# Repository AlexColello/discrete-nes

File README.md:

# Discrete NES - Every Gate Visible

A discrete logic implementation of the Nintendo Entertainment System where **EVERY single gate output and EVERY memory bit is visible via LED**. Watch a complete NES flip every bit in real-time.

## Project Vision

This is an educational and artistic hardware project showcasing the complete internal state of a working NES using **TI Little Logic (SN74LVC1G) in DSBGA packages** — tiny ICs with the **bare silicon die visible** on top. Thousands of exposed silicon dies interspersed with glowing 0402 SMD LEDs.

**This is one of the largest discrete logic projects ever attempted:**
- Estimated **10,000+ LEDs** across all boards
- **Thousands of single-gate ICs** (TI Little Logic, DSBGA — bare silicon visible)
- Multiple PCBs with SMD assembly
- Complete **cycle-accurate NES** implementation in visible discrete logic

## The Aesthetic

Each logic gate is a single DSBGA package (1.75 x 1.25mm) with the bare silicon wafer pattern visible on top. Between them, tiny 0402 SMD LEDs (1.0 x 0.5mm) glow to show every gate output state. The LEDs are deliberately smaller than the ICs so the silicon dies are the visual focus.

## Board Structure

- **RAM Board** - 8-byte prototype (starting point, validates DSBGA assembly)
  - ~180 DSBGA ICs, ~115 LEDs, ~115 resistors
  - ~60x80mm PCB

- **CPU Board** (2A03 - 6502-based with APU)
  - ~5,000 LEDs, ~5,000 ICs

- **PPU Board** (2C02 - Picture Processing Unit)
  - ~3,000 LEDs, ~3,000 ICs

- **Glue Logic/Interconnect Boards**

## Technology Stack

- **Logic ICs:** TI Little Logic SN74LVC1G series (DSBGA — bare silicon die visible)
- **LEDs:** 0402 SMD (smaller than ICs for aesthetic balance)
- **LED Drive:** Direct from LVC outputs (up to 24mA capable, target 2mA)
- **Schematic Generation:** Python + kiutils
- **PCB Layout:** kiutils + manual routing
- **Logic Reference:** MiSTer NES core (Verilog/SystemVerilog)
- **Design Tool:** KiCad 8.x
- **Assembly:** Solder paste stencil + hot air reflow

## Repository Structure

```
discrete-nes/
├── shared/               # Shared libraries and utilities
│   ├── kicad-lib/       # KiCad symbols, footprints, 3D models
│   └── python/          # Python generation utilities
├── boards/              # Individual board projects
│   ├── ram-prototype/   # First prototype board (8 bytes)
│   ├── cpu-2a03/        # CPU board
│   ├── ppu-2c02/        # PPU board
│   └── interconnect/    # Board interconnection
├── reference/           # FPGA reference documentation
└── tools/               # Development tools
```

## Getting Started

### Prerequisites

- Python 3.8+
- KiCad 8.x
- Git

### Setup

1. **Clone this repository:**
   ```bash
   git clone https://github.com/yourusername/discrete-nes.git
   cd discrete-nes
   ```

2. **Set up Python environment:**
   ```bash
   python -m venv venv
   source venv/bin/activate  # On Windows: venv\Scripts\activate
   pip install -r requirements.txt
   ```

3. **Review the reference documentation:**
   See `reference/README.md` for information about accessing the MiSTer NES core used as logic reference.

## Development Workflow

1. **Design circuit manually** in KiCad (first cell/module)
2. **Document the pattern** for script generation
3. **Write Python scripts** to generate repetitive structures
4. **Generate schematics** using kiutils
5. **Place components** on PCB (scripted DSBGA grid layout)
6. **Route manually** or use assisted tools
7. **Validate** with DRC/ERC
8. **Fabricate and reflow assemble**

## Current Status

**Phase 1: Project Setup** - COMPLETE

- [x] Repository structure created
- [x] Python utilities framework
- [x] Reference documentation
- [x] KiCad shared libraries (symbols/footprints)
- [x] Migration to TI Little Logic DSBGA
- [ ] RAM prototype circuit design (next)

## Power Requirements

With an LED on every gate output, power consumption is LED-dominated:

- RAM prototype (8 bytes): ~0.25A at 3.3V (~0.8W)
- Full system: ~12A+ at 3.3V (~40W)

## Educational Value

This project provides unparalleled visibility into:
- How a CPU executes instructions (watch the program counter increment!)
- Memory addressing and data flow
- Video frame generation in real-time
- Every internal state transition

Perfect for computer science education, maker spaces, and museum exhibits.

## Resources

- **MiSTer NES Core:** https://github.com/MiSTer-devel/NES_MiSTer (logic reference)
- **OpenTendo:** https://github.com/Redherring32/OpenTendo (NES reproduction PCBs)
- **NES Dev Wiki:** https://www.nesdev.org/wiki/
- **Visual 6502:** http://www.visual6502.org/

## Contributing

This is an ambitious project that will evolve over time. Contributions welcome:
- Circuit design improvements
- Python generation utilities
- Documentation
- Testing and validation

## License

TBD - To be determined

## Acknowledgments

- **MiSTer Project** - For the excellent NES core used as logic reference
- **Texas Instruments** - For the Little Logic product line
- **KiCad Project** - For the outstanding open-source EDA tools
- **Ben Eater** - For inspiring discrete logic projects
- **NES Dev Community** - For extensive documentation

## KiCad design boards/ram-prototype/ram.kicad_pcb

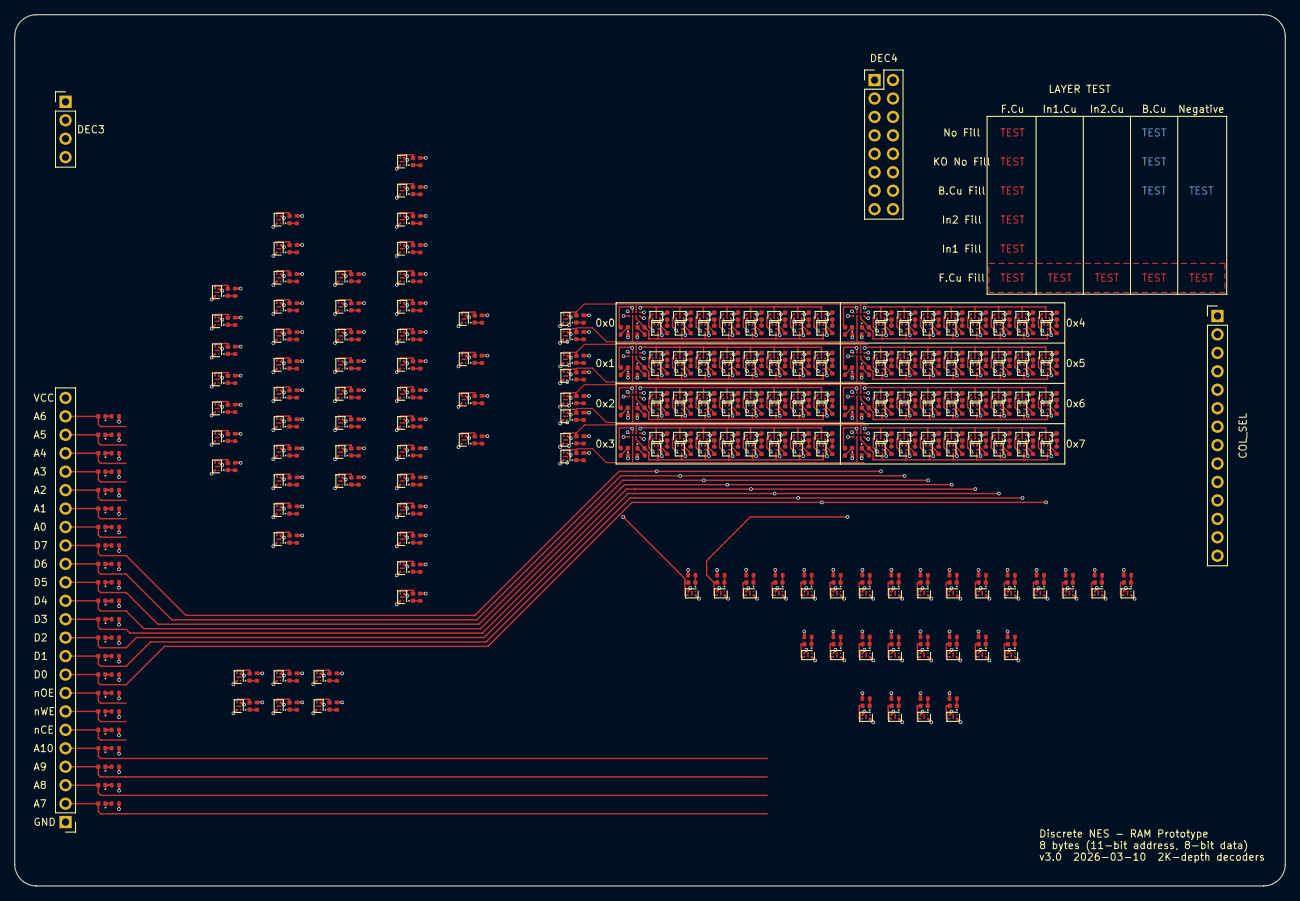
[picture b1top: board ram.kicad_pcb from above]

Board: 4 copper layers, 175.0 x 120.0 mm, 611 parts (1 on the bottom side), 384 nets.

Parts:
D1, D2, D3, D4, D5, D6, D7, D8, D9, D10, D11, D12, D13, D14, D15, D16, D17, D18, D19, D20, D21, D22, D23, D24, D25, D26, D27, D28, D29, D30, D31, D32, D33, D34, D35, D36, D37, D38, D39, D40, D41, D42, D43, D44, D45, D46, D47, D48, D49, D50, D51, D52, D53, D54, D55, D56, D57, D58, D59, D60, D61, D62, D63, D64, D65, D66, D67, D68, D69, D70, D71, D72, D73, D74, D75, D76, D77, D78, D79, D80, D81, D82, D83, D84, D85, D86, D87, D88, D89, D90, D91, D92, D93, D94, D95, D96, D97, D98, D99, D100, D101, D102, D103, D104, D105, D106, D107, D108, D109, D110, D111, D112, D113, D114, D115, D116, D117, D118, D119, D120, D121, D122, D123, D124, D125, D126, D127, D128, D129, D130, D131, D132, D133, D134, D135, D136, D137, D138, D139, D140, D141, D142, D143, D144, D145, D146, D147, D148, D149, D150, D151, D152, D153, D154, D155, D156, D157, D158, D159, D160, D161, D162, D163, D164, D165, D166, D167, D168, D169, D170, D171, D172, D173, D174, D175, D176, D177, D178, D179, D180, D181, D182, D183, D184, D185, D187, D188, D189, D190, D191, D192: LED_0402_1005Metric
J1: PinHeader_1x24_P2.54mm_Vertical
J2: PinHeader_1x04_P2.54mm_Vertical
J3: PinHeader_1x14_P2.54mm_Vertical
J4: PinHeader_2x08_P2.54mm_Vertical
R1, R2, R3, R4, R5, R6, R7, R8, R9, R10, R11, R12, R13, R14, R15, R16, R17, R18, R19, R20, R21, R22, R23, R24, R25, R26, R27, R28, R29, R30, R31, R32, R33, R34, R35, R36, R37, R38, R39, R40, R41, R42, R43, R44, R45, R46, R47, R48, R49, R50, R51, R52, R53, R54, R55, R56, R57, R58, R59, R60, R61, R62, R63, R64, R65, R66, R67, R68, R69, R70, R71, R72, R73, R74, R75, R76, R77, R78, R79, R80, R81, R82, R83, R84, R85, R86, R87, R88, R89, R90, R91, R92, R93, R94, R95, R96, R97, R98, R99, R100, R101, R102, R103, R104, R105, R106, R107, R108, R109, R110, R111, R112, R113, R114, R115, R116, R117, R118, R119, R120, R121, R122, R123, R124, R125, R126, R127, R128, R129, R130, R131, R132, R133, R134, R135, R136, R137, R138, R139, R140, R141, R142, R143, R144, R145, R146, R147, R148, R149, R150, R151, R152, R153, R154, R155, R156, R157, R158, R159, R160, R161, R162, R163, R164, R165, R166, R167, R168, R169, R170, R171, R172, R173, R174, R175, R176, R177, R178, R179, R180, R181, R182, R183, R184, R185, R190, R191, R192, R193, R194, R195: R_0402_1005Metric
U1, U2, U3, U4, U5, U6, U7, U8, U9, U10, U11, U12, U13, U14, U15, U16, U17, U18, U19, U20, U21, U22, U23, U24, U25, U26, U27, U28, U29, U30, U31, U32, U33, U34, U35, U36, U37, U38, U39, U40, U41, U42, U43, U44, U45, U46, U47, U48, U49, U50, U51, U52, U53, U54, U55, U56, U57, U58, U59, U60, U61, U62, U63, U64, U65, U66, U67, U68, U69, U70, U71, U72, U73, U74, U75, U76, U77, U78, U79, U80, U81, U82, U83, U92, U93, U94, U95, U96, U97, U98, U99, U100, U101, U102, U103, U104, U105, U106, U107, U108, U109, U110, U111, U112, U113, U114, U115, U116, U117, U118, U119, U120, U121, U122, U123, U124, U125, U126, U127, U128, U129, U130, U131, U132, U133, U134, U135, U136, U137, U138, U139, U140, U141, U142, U143, U144, U145, U146, U147, U148, U149, U150, U151, U152, U153, U154, U155, U156, U157, U158, U159, U160, U161, U162, U163, U164, U165, U166, U167, U168, U169, U170, U171, U172, U173, U174, U175, U176, U177, U178, U179, U180, U181, U182, U183, U184, U185, U186, U187, U188, U189, U190, U191, U192, U193, U194, U195, U196, U197, U198, U199, U200, U201, U202, U203, U204, U205, U206, U207, U208, U209, U210, U211, U212, U213, U214, U215, U216, U217, U218, U219, U221, U222, U223, U224, U225, U226: DSBGA\-5_NumericPads; DSBGA-5_NumericPads
U84, U85, U86, U87, U88, U89, U90, U91: DSBGA\-8_NumericPads; DSBGA-8_NumericPads

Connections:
/Address Decoder/A0: D7.2, J1.17, U7.2, U13.2, U15.2, U17.2, U19.2
/Address Decoder/A1: D6.2, J1.18, U6.2, U9.2, U11.2
/Address Decoder/A2: D5.2, J1.19, U5.2, U10.1, U11.1
/Address Decoder/A3: D4.2, J1.20, U4.2, U21.2, U23.2
/Address Decoder/A4: D3.2, J1.21, U3.2, U22.1, U23.1
/Address Decoder/A5: D2.2, J1.22, U2.2, U25.2, U27.2
/Address Decoder/A6: D1.2, J1.23, U1.2, U26.1, U27.1
/Address Decoder/DEC3_0: D34.2, U12.4, U44.1
/Address Decoder/DEC3_1: D35.2, U13.4, U45.1
/Address Decoder/DEC3_2: D36.2, U14.4, U46.1
/Address Decoder/DEC3_3: D37.2, U15.4, U47.1
/Address Decoder/DEC4_0: D50.2, U28.4, U44.2, U45.2, U46.2, U47.2
/Address Decoder/G0: D30.2, U8.4, U12.1, U13.1
/Address Decoder/G1: D31.2, U9.4, U14.1, U15.1
/Address Decoder/G2: D32.2, U10.4, U16.1, U17.1
/Address Decoder/G3: D33.2, U11.4, U18.1, U19.1
/Address Decoder/HA0: D42.2, U20.4, U28.2, U32.2, U36.2, U40.2
/Address Decoder/HA1: D43.2, U21.4, U29.2, U33.2, U37.2, U41.2
/Address Decoder/HA2: D44.2, U22.4, U30.2, U34.2, U38.2, U42.2
/Address Decoder/HA3: D45.2, U23.4, U31.2, U35.2, U39.2, U43.2
/Address Decoder/HB0: D46.2, U24.4, U28.1, U29.1, U30.1, U31.1
/Address Decoder/HB1: D47.2, U25.4, U32.1, U33.1, U34.1, U35.1
/Address Decoder/HB2: D48.2, U26.4, U36.1, U37.1, U38.1, U39.1
/Address Decoder/HB3: D49.2, U27.4, U40.1, U41.1, U42.1, U43.1
/Address Decoder/ROW_SEL_0: D66.2, U44.4, U76.2, U80.2
/Address Decoder/ROW_SEL_1: D67.2, U45.4, U77.2, U81.2
/Address Decoder/ROW_SEL_2: D68.2, U46.4, U78.2, U82.2
/Address Decoder/ROW_SEL_3: D69.2, U47.4, U79.2, U83.2
/Address Decoder/nA0: D29.2, U7.4, U12.2, U14.2, U16.2, U18.2
/Address Decoder/nA1: D28.2, U6.4, U8.2, U10.2
/Address Decoder/nA2: D27.2, U5.4, U8.1, U9.1
/Address Decoder/nA3: D26.2, U4.4, U20.2, U22.2
/Address Decoder/nA4: D25.2, U3.4, U20.1, U21.1
/Address Decoder/nA5: D24.2, U2.4, U24.2, U26.2
/Address Decoder/nA6: D23.2, U1.4, U24.1, U25.1
/COL_SEL_0: D82.2, U60.4, U84.1, U84.5, U85.1, U85.5, U86.1, U86.5, U87.1, U87.5
/COL_SEL_1: D83.2, U61.4, U88.1, U88.5, U89.1, U89.5, U90.1, U90.5, U91.1, U91.5
/COL_SEL_2: D84.2, J3.1, U62.4
/COL_SEL_3: D85.2, J3.2, U63.4
/COL_SEL_4: D86.2, J3.3, U64.4
/COL_SEL_5: D87.2, J3.4, U65.4
/COL_SEL_6: D88.2, J3.5, U66.4
/COL_SEL_7: D89.2, J3.6, U67.4
/COL_SEL_8: D90.2, J3.7, U68.4
/COL_SEL_9: D91.2, J3.8, U69.4
/COL_SEL_10: D92.2, J3.9, U70.4
/COL_SEL_11: D93.2, J3.10, U71.4
/COL_SEL_12: D94.2, J3.11, U72.4
/COL_SEL_13: D95.2, J3.12, U73.4
/COL_SEL_14: D96.2, J3.13, U74.4
/COL_SEL_15: D97.2, J3.14, U75.4
/Column Select/A7: D22.2, J1.2, U48.2, U53.2, U55.2
/Column Select/A8: D21.2, J1.3, U49.2, U54.1, U55.1
/Column Select/A9: D20.2, J1.4, U50.2, U57.2, U59.2
/Column Select/A10: D19.2, J1.5, U51.2, U58.1, U59.1
/Column Select/GA0: D74.2, U52.4, U60.2, U64.2, U68.2, U72.2
/Column Select/GA1: D75.2, U53.4, U61.2, U65.2, U69.2, U73.2
/Column Select/GA2: D76.2, U54.4, U62.2, U66.2, U70.2, U74.2
/Column Select/GA3: D77.2, U55.4, U63.2, U67.2, U71.2, U75.2
/Column Select/GB0: D78.2, U56.4, U60.1, U61.1, U62.1, U63.1
/Column Select/GB1: D79.2, U57.4, U64.1, U65.1, U66.1, U67.1
/Column Select/GB2: D80.2, U58.4, U68.1, U69.1, U70.1, U71.1
/Column Select/GB3: D81.2, U59.4, U72.1, U73.1, U74.1, U75.1
/D0: D15.2, J1.9, U92.1, U93.1, U94.1, U95.1, U96.1, U97.1, U98.1, U99.1, U100.4, U101.4, U102.4, U103.4, U104.4, U105.4, U106.4, U107.4
/D1: D14.2, J1.10, U108.1, U109.1, U110.1, U111.1, U112.1, U113.1, U114.1, U115.1, U116.4, U117.4, U118.4, U119.4, U120.4, U121.4, U122.4, U123.4
/D2: D13.2, J1.11, U124.1, U125.1, U126.1, U127.1, U128.1, U129.1, U130.1, U131.1, U132.4, U133.4, U134.4, U135.4, U136.4, U137.4, U138.4, U139.4
/D3: D12.2, J1.12, U140.1, U141.1, U142.1, U143.1, U144.1, U145.1, U146.1, U147.1, U148.4, U149.4, U150.4, U151.4, U152.4, U153.4, U154.4, U155.4
/D4: D11.2, J1.13, U156.1, U157.1, U158.1, U159.1, U160.1, U161.1, U162.1, U163.1, U164.4, U165.4, U166.4, U167.4, U168.4, U169.4, U170.4, U171.4
/D5: D10.2, J1.14, U172.1, U173.1, U174.1, U175.1, U176.1, U177.1, U178.1, U179.1, U180.4, U181.4, U182.4, U183.4, U184.4, U185.4, U186.4, U187.4
/D6: D9.2, J1.15, U188.1, U189.1, U190.1, U191.1, U192.1, U193.1, U194.1, U195.1, U196.4, U197.4, U198.4, U199.4, U200.4, U201.4, U202.4, U203.4
/D7: D8.2, J1.16, U204.1, U205.1, U206.1, U207.1, U208.1, U209.1, U210.1, U211.1, U212.4, U213.4, U214.4, U215.4, U216.4, U217.4, U218.4, U219.4
/DEC3_4: D38.2, J2.1, U16.4
/DEC3_5: D39.2, J2.2, U17.4
/DEC3_6: D40.2, J2.3, U18.4
/DEC3_7: D41.2, J2.4, U19.4
/DEC4_1: D51.2, J4.1, U29.4
/DEC4_2: D52.2, J4.2, U30.4
/DEC4_3: D53.2, J4.3, U31.4
/DEC4_4: D54.2, J4.4, U32.4
/DEC4_5: D55.2, J4.5, U33.4
/DEC4_6: D56.2, J4.6, U34.4
/DEC4_7: D57.2, J4.7, U35.4
/DEC4_8: D58.2, J4.8, U36.4
/DEC4_9: D59.2, J4.9, U37.4
/DEC4_10: D60.2, J4.10, U38.4
/DEC4_11: D61.2, J4.11, U39.4
/DEC4_12: D62.2, J4.12, U40.4
/DEC4_13: D63.2, J4.13, U41.4
/DEC4_14: D64.2, J4.14, U42.4
/DEC4_15: D65.2, J4.15, U43.4
/READ_EN: D192.2, U80.1, U81.1, U82.1, U83.1, U226.4
/READ_EN_ROW_0: D102.2, U80.4, U84.6, U88.6
/READ_EN_ROW_1: D103.2, U81.4, U85.6, U89.6
/READ_EN_ROW_2: D104.2, U82.4, U86.6, U90.6
/READ_EN_ROW_3: D105.2, U83.4, U87.6, U91.6
/WRITE_ACTIVE: D191.2, U76.1, U77.1, U78.1, U79.1, U224.4
/WRITE_EN_ROW_0: D98.2, U76.4, U84.2, U88.2
/WRITE_EN_ROW_1: D99.2, U77.4, U85.2, U89.2
/WRITE_EN_ROW_2: D100.2, U78.4, U86.2, U90.2
/WRITE_EN_ROW_3: D101.2, U79.4, U87.2, U91.2
/nCE: D16.2, J1.8, U221.2
/nOE: D17.2, J1.7, U222.2
/nWE: D18.2, J1.6, U223.2, U226.2
GND: J1.1, J4.16, R1.2, R2.2, R3.2, R4.2, R5.2, R6.2, R7.2, R8.2, R9.2, R10.2, R11.2, R12.2, R13.2, R14.2, R15.2, R16.2, R17.2, R18.2, R19.2, R20.2, R21.2, R22.2, R23.2, R24.2, R25.2, R26.2, R27.2, R28.2, R29.2, R30.2, R31.2, R32.2, R33.2, R34.2, R35.2, R36.2, R37.2, R38.2, R39.2, R40.2, R41.2, R42.2, R43.2, R44.2, R45.2, R46.2, R47.2, R48.2, R49.2, R50.2, R51.2, R52.2, R53.2, R54.2, R55.2, R56.2, R57.2, R58.2, R59.2, R60.2, R61.2, R62.2, R63.2, R64.2, R65.2, R66.2, R67.2, R68.2, R69.2, R70.2, R71.2, R72.2, R73.2, R74.2, R75.2, R76.2, R77.2, R78.2, R79.2, R80.2, R81.2, R82.2, R83.2, R84.2, R85.2, R86.2, R87.2, R88.2, R89.2, R90.2, R91.2, R92.2, R93.2, R94.2, R95.2, R96.2, R97.2, R98.2, R99.2, R100.2, R101.2, R102.2, R103.2, R104.2, R105.2, R106.2, R107.2, R108.2, R109.2, R110.2, R111.2, R112.2, R113.2, R114.2, R115.2, R116.2, R117.2, R118.2, R119.2, R120.2, R121.2, R122.2, R123.2, R124.2, R125.2, R126.2, R127.2, R128.2, R129.2, R130.2, R131.2, R132.2, R133.2, R134.2, R135.2, R136.2, R137.2, R138.2, R139.2, R140.2, R141.2, R142.2, R143.2, R144.2, R145.2, R146.2, R147.2, R148.2, R149.2, R150.2, R151.2, R152.2, R153.2, R154.2, R155.2, R156.2, R157.2, R158.2, R159.2, R160.2, R161.2, R162.2, R163.2, R164.2, R165.2, R166.2, R167.2, R168.2, R169.2, R170.2, R171.2, R172.2, R173.2, R174.2, R175.2, R176.2, R177.2, R178.2, R179.2, R180.2, R181.2, R182.2, R183.2, R184.2, R185.2, R190.2, R191.2, R192.2, R193.2, R194.2, R195.2, U1.3, U2.3, U3.3, U4.3, U5.3, U6.3, U7.3, U8.3, U9.3, U10.3, U11.3, U12.3, U13.3, U14.3, U15.3, U16.3, U17.3, U18.3, U19.3, U20.3, U21.3, U22.3, U23.3, U24.3, U25.3, U26.3, U27.3, U28.3, U29.3, U30.3, U31.3, U32.3, U33.3, U34.3, U35.3, U36.3, U37.3, U38.3, U39.3, U40.3, U41.3, U42.3, U43.3, U44.3, U45.3, U46.3, U47.3, U48.3, U49.3, U50.3, U51.3, U52.3, U53.3, U54.3, U55.3, U56.3, U57.3, U58.3, U59.3, U60.3, U61.3, U62.3, U63.3, U64.3, U65.3, U66.3, U67.3, U68.3, U69.3, U70.3, U71.3, U72.3, U73.3, U74.3, U75.3, U76.3, U77.3, U78.3, U79.3, U80.3, U81.3, U82.3, U83.3, U84.4, U85.4, U86.4, U87.4, U88.4, U89.4, U90.4, U91.4, U92.3, U93.3, U94.3, U95.3, U96.3, U97.3, U98.3, U99.3, U100.3, U101.3, U102.3, U103.3, U104.3, U105.3, U106.3, U107.3, U108.3, U109.3, U110.3, U111.3, U112.3, U113.3, U114.3, U115.3, U116.3, U117.3, U118.3, U119.3, U120.3, U121.3, U122.3, U123.3, U124.3, U125.3, U126.3, U127.3, U128.3, U129.3, U130.3, U131.3, U132.3, U133.3, U134.3, U135.3, U136.3, U137.3, U138.3, U139.3, U140.3, U141.3, U142.3, U143.3, U144.3, U145.3, U146.3, U147.3, U148.3, U149.3, U150.3, U151.3, U152.3, U153.3, U154.3, U155.3, U156.3, U157.3, U158.3, U159.3, U160.3, U161.3, U162.3, U163.3, U164.3, U165.3, U166.3, U167.3, U168.3, U169.3, U170.3, U171.3, U172.3, U173.3, U174.3, U175.3, U176.3, U177.3, U178.3, U179.3, U180.3, U181.3, U182.3, U183.3, U184.3, U185.3, U186.3, U187.3, U188.3, U189.3, U190.3, U191.3, U192.3, U193.3, U194.3, U195.3, U196.3, U197.3, U198.3, U199.3, U200.3, U201.3, U202.3, U203.3, U204.3, U205.3, U206.3, U207.3, U208.3, U209.3, U210.3, U211.3, U212.3, U213.3, U214.3, U215.3, U216.3, U217.3, U218.3, U219.3, U221.3, U222.3, U223.3, U224.3, U225.3, U226.3
unnamed: D1.1, R1.1
unnamed: D2.1, R2.1
unnamed: D3.1, R3.1
unnamed: D4.1, R4.1
unnamed: D5.1, R5.1
unnamed: D6.1, R6.1
unnamed: D7.1, R7.1
unnamed: D8.1, R8.1
unnamed: D9.1, R9.1
unnamed: D10.1, R10.1
unnamed: D11.1, R11.1
unnamed: D12.1, R12.1
unnamed: D13.1, R13.1
unnamed: D14.1, R14.1
unnamed: D15.1, R15.1
unnamed: D16.1, R16.1
unnamed: D17.1, R17.1
unnamed: D18.1, R18.1
unnamed: D19.1, R19.1
unnamed: D20.1, R20.1
unnamed: D21.1, R21.1
unnamed: D22.1, R22.1
unnamed: D23.1, R23.1
unnamed: D24.1, R24.1
unnamed: D25.1, R25.1
unnamed: D26.1, R26.1
unnamed: D27.1, R27.1
unnamed: D28.1, R28.1
unnamed: D29.1, R29.1
unnamed: D30.1, R30.1
unnamed: D31.1, R31.1
unnamed: D32.1, R32.1
unnamed: D33.1, R33.1
unnamed: D34.1, R34.1
unnamed: D35.1, R35.1
unnamed: D36.1, R36.1
unnamed: D37.1, R37.1
unnamed: D38.1, R38.1
unnamed: D39.1, R39.1
unnamed: D40.1, R40.1
unnamed: D41.1, R41.1
unnamed: D42.1, R42.1
unnamed: D43.1, R43.1
unnamed: D44.1, R44.1
unnamed: D45.1, R45.1
unnamed: D46.1, R46.1
unnamed: D47.1, R47.1
unnamed: D48.1, R48.1
unnamed: D49.1, R49.1
unnamed: D50.1, R50.1
unnamed: D51.1, R51.1
unnamed: D52.1, R52.1
unnamed: D53.1, R53.1
unnamed: D54.1, R54.1
unnamed: D55.1, R55.1
unnamed: D56.1, R56.1
unnamed: D57.1, R57.1
unnamed: D58.1, R58.1
unnamed: D59.1, R59.1
unnamed: D60.1, R60.1
unnamed: D61.1, R61.1
unnamed: D62.1, R62.1
unnamed: D63.1, R63.1
unnamed: D64.1, R64.1
unnamed: D65.1, R65.1
unnamed: D66.1, R66.1
unnamed: D67.1, R67.1
unnamed: D68.1, R68.1
unnamed: D69.1, R69.1
unnamed: D70.2, U48.4, U52.2, U54.2
unnamed: D70.1, R70.1
unnamed: D71.2, U49.4, U52.1, U53.1
unnamed: D71.1, R71.1
unnamed: D72.2, U50.4, U56.2, U58.2
unnamed: D72.1, R72.1
unnamed: D73.2, U51.4, U56.1, U57.1
unnamed: D73.1, R73.1
unnamed: D74.1, R74.1
unnamed: D75.1, R75.1
unnamed: D76.1, R76.1
unnamed: D77.1, R77.1
unnamed: D78.1, R78.1
unnamed: D79.1, R79.1
unnamed: D80.1, R80.1
unnamed: D81.1, R81.1
unnamed: D82.1, R82.1
unnamed: D83.1, R83.1
unnamed: D84.1, R84.1
unnamed: D85.1, R85.1
unnamed: D86.1, R86.1
unnamed: D87.1, R87.1
unnamed: D88.1, R88.1
unnamed: D89.1, R89.1
unnamed: D90.1, R90.1
unnamed: D91.1, R91.1
unnamed: D92.1, R92.1
unnamed: D93.1, R93.1
unnamed: D94.1, R94.1
unnamed: D95.1, R95.1
unnamed: D96.1, R96.1
unnamed: D97.1, R97.1
unnamed: D98.1, R98.1
unnamed: D99.1, R99.1
unnamed: D100.1, R100.1
unnamed: D101.1, R101.1
unnamed: D102.1, R102.1
unnamed: D103.1, R103.1
unnamed: D104.1, R104.1
unnamed: D105.1, R105.1
unnamed: D106.2, U84.7, U92.2, U108.2, U124.2, U140.2, U156.2, U172.2, U188.2, U204.2
unnamed: D106.1, R106.1
unnamed: D107.2, U85.7, U93.2, U109.2, U125.2, U141.2, U157.2, U173.2, U189.2, U205.2
unnamed: D107.1, R107.1
unnamed: D108.2, U86.7, U94.2, U110.2, U126.2, U142.2, U158.2, U174.2, U190.2, U206.2
unnamed: D108.1, R108.1
unnamed: D109.2, U87.7, U95.2, U111.2, U127.2, U143.2, U159.2, U175.2, U191.2, U207.2
unnamed: D109.1, R109.1
unnamed: D110.2, U88.7, U96.2, U112.2, U128.2, U144.2, U160.2, U176.2, U192.2, U208.2
unnamed: D110.1, R110.1
unnamed: D111.2, U89.7, U97.2, U113.2, U129.2, U145.2, U161.2, U177.2, U193.2, U209.2
unnamed: D111.1, R111.1
unnamed: D112.2, U90.7, U98.2, U114.2, U130.2, U146.2, U162.2, U178.2, U194.2, U210.2
unnamed: D112.1, R112.1
unnamed: D113.2, U91.7, U99.2, U115.2, U131.2, U147.2, U163.2, U179.2, U195.2, U211.2
unnamed: D113.1, R113.1
unnamed: D114.2, U84.3, U100.1, U116.1, U132.1, U148.1, U164.1, U180.1, U196.1, U212.1
unnamed: D114.1, R114.1
unnamed: D115.2, U85.3, U101.1, U117.1, U133.1, U149.1, U165.1, U181.1, U197.1, U213.1
unnamed: D115.1, R115.1
unnamed: D116.2, U86.3, U102.1, U118.1, U134.1, U150.1, U166.1, U182.1, U198.1, U214.1
unnamed: D116.1, R116.1
unnamed: D117.2, U87.3, U103.1, U119.1, U135.1, U151.1, U167.1, U183.1, U199.1, U215.1
unnamed: D117.1, R117.1
unnamed: D118.2, U88.3, U104.1, U120.1, U136.1, U152.1, U168.1, U184.1, U200.1, U216.1
unnamed: D118.1, R118.1
unnamed: D119.2, U89.3, U105.1, U121.1, U137.1, U153.1, U169.1, U185.1, U201.1, U217.1
unnamed: D119.1, R119.1
unnamed: D120.2, U90.3, U106.1, U122.1, U138.1, U154.1, U170.1, U186.1, U202.1, U218.1
unnamed: D120.1, R120.1
unnamed: D121.2, U91.3, U107.1, U123.1, U139.1, U155.1, U171.1, U187.1, U203.1, U219.1
unnamed: D121.1, R121.1
unnamed: D122.2, U92.4, U100.2
unnamed: D122.1, R122.1
unnamed: D123.2, U93.4, U101.2
unnamed: D123.1, R123.1
unnamed: D124.2, U94.4, U102.2
unnamed: D124.1, R124.1
unnamed: D125.2, U95.4, U103.2
unnamed: D125.1, R125.1
unnamed: D126.2, U96.4, U104.2
unnamed: D126.1, R126.1
unnamed: D127.2, U97.4, U105.2
unnamed: D127.1, R127.1
unnamed: D128.2, U98.4, U106.2
unnamed: D128.1, R128.1
unnamed: D129.2, U99.4, U107.2
unnamed: D129.1, R129.1
unnamed: D130.2, U108.4, U116.2
unnamed: D130.1, R130.1
unnamed: D131.2, U109.4, U117.2
unnamed: D131.1, R131.1
unnamed: D132.2, U110.4, U118.2
unnamed: D132.1, R132.1
unnamed: D133.2, U111.4, U119.2
unnamed: D133.1, R133.1
unnamed: D134.2, U112.4, U120.2
unnamed: D134.1, R134.1
unnamed: D135.2, U113.4, U121.2
unnamed: D135.1, R135.1
unnamed: D136.2, U114.4, U122.2
unnamed: D136.1, R136.1
unnamed: D137.2, U115.4, U123.2
unnamed: D137.1, R137.1
unnamed: D138.2, U124.4, U132.2
unnamed: D138.1, R138.1
unnamed: D139.2, U125.4, U133.2
unnamed: D139.1, R139.1
unnamed: D140.2, U126.4, U134.2
unnamed: D140.1, R140.1
unnamed: D141.2, U127.4, U135.2
unnamed: D141.1, R141.1
unnamed: D142.2, U128.4, U136.2
unnamed: D142.1, R142.1
unnamed: D143.2, U129.4, U137.2
unnamed: D143.1, R143.1
unnamed: D144.2, U130.4, U138.2
unnamed: D144.1, R144.1
unnamed: D145.2, U131.4, U139.2
unnamed: D145.1, R145.1
unnamed: D146.2, U140.4, U148.2
unnamed: D146.1, R146.1
unnamed: D147.2, U141.4, U149.2
unnamed: D147.1, R147.1
unnamed: D148.2, U142.4, U150.2
unnamed: D148.1, R148.1
unnamed: D149.2, U143.4, U151.2
unnamed: D149.1, R149.1
unnamed: D150.2, U144.4, U152.2
unnamed: D150.1, R150.1
unnamed: D151.2, U145.4, U153.2
unnamed: D151.1, R151.1
unnamed: D152.2, U146.4, U154.2
unnamed: D152.1, R152.1
unnamed: D153.2, U147.4, U155.2
unnamed: D153.1, R153.1
unnamed: D154.2, U156.4, U164.2
unnamed: D154.1, R154.1
unnamed: D155.2, U157.4, U165.2
unnamed: D155.1, R155.1
unnamed: D156.2, U158.4, U166.2
unnamed: D156.1, R156.1
unnamed: D157.2, U159.4, U167.2
unnamed: D157.1, R157.1
unnamed: D158.2, U160.4, U168.2
unnamed: D158.1, R158.1
unnamed: D159.2, U161.4, U169.2
unnamed: D159.1, R159.1
unnamed: D160.2, U162.4, U170.2
unnamed: D160.1, R160.1
unnamed: D161.2, U163.4, U171.2
unnamed: D161.1, R161.1
unnamed: D162.2, U172.4, U180.2
unnamed: D162.1, R162.1
unnamed: D163.2, U173.4, U181.2
unnamed: D163.1, R163.1
unnamed: D164.2, U174.4, U182.2
unnamed: D164.1, R164.1
unnamed: D165.2, U175.4, U183.2
unnamed: D165.1, R165.1
unnamed: D166.2, U176.4, U184.2
unnamed: D166.1, R166.1
unnamed: D167.2, U177.4, U185.2
unnamed: D167.1, R167.1
unnamed: D168.2, U178.4, U186.2
unnamed: D168.1, R168.1
unnamed: D169.2, U179.4, U187.2
unnamed: D169.1, R169.1
unnamed: D170.2, U188.4, U196.2
unnamed: D170.1, R170.1
unnamed: D171.2, U189.4, U197.2
unnamed: D171.1, R171.1
unnamed: D172.2, U190.4, U198.2
unnamed: D172.1, R172.1
unnamed: D173.2, U191.4, U199.2
unnamed: D173.1, R173.1
unnamed: D174.2, U192.4, U200.2
unnamed: D174.1, R174.1
unnamed: D175.2, U193.4, U201.2
unnamed: D175.1, R175.1
unnamed: D176.2, U194.4, U202.2
unnamed: D176.1, R176.1
unnamed: D177.2, U195.4, U203.2
unnamed: D177.1, R177.1
unnamed: D178.2, U204.4, U212.2
unnamed: D178.1, R178.1
unnamed: D179.2, U205.4, U213.2
unnamed: D179.1, R179.1
unnamed: D180.2, U206.4, U214.2
unnamed: D180.1, R180.1
unnamed: D181.2, U207.4, U215.2
unnamed: D181.1, R181.1
unnamed: D182.2, U208.4, U216.2
unnamed: D182.1, R182.1
unnamed: D183.2, U209.4, U217.2
unnamed: D183.1, R183.1
unnamed: D184.2, U210.4, U218.2
unnamed: D184.1, R184.1
unnamed: D185.2, U211.4, U219.2
unnamed: D185.1, R185.1
unnamed: D187.2, U221.4, U224.1, U225.1
unnamed: D187.1, R190.1
unnamed: D188.2, U222.4, U225.2
unnamed: D188.1, R191.1
unnamed: D189.2, U223.4, U224.2
unnamed: D189.1, R192.1
unnamed: D190.2, U225.4, U226.1
unnamed: D190.1, R193.1
unnamed: D191.1, R194.1
unnamed: D192.1, R195.1
VCC: J1.24, U1.5, U2.5, U3.5, U4.5, U5.5, U6.5, U7.5, U8.5, U9.5, U10.5, U11.5, U12.5, U13.5, U14.5, U15.5, U16.5, U17.5, U18.5, U19.5, U20.5, U21.5, U22.5, U23.5, U24.5, U25.5, U26.5, U27.5, U28.5, U29.5, U30.5, U31.5, U32.5, U33.5, U34.5, U35.5, U36.5, U37.5, U38.5, U39.5, U40.5, U41.5, U42.5, U43.5, U44.5, U45.5, U46.5, U47.5, U48.5, U49.5, U50.5, U51.5, U52.5, U53.5, U54.5, U55.5, U56.5, U57.5, U58.5, U59.5, U60.5, U61.5, U62.5, U63.5, U64.5, U65.5, U66.5, U67.5, U68.5, U69.5, U70.5, U71.5, U72.5, U73.5, U74.5, U75.5, U76.5, U77.5, U78.5, U79.5, U80.5, U81.5, U82.5, U83.5, U84.8, U85.8, U86.8, U87.8, U88.8, U89.8, U90.8, U91.8, U92.5, U93.5, U94.5, U95.5, U96.5, U97.5, U98.5, U99.5, U100.5, U101.5, U102.5, U103.5, U104.5, U105.5, U106.5, U107.5, U108.5, U109.5, U110.5, U111.5, U112.5, U113.5, U114.5, U115.5, U116.5, U117.5, U118.5, U119.5, U120.5, U121.5, U122.5, U123.5, U124.5, U125.5, U126.5, U127.5, U128.5, U129.5, U130.5, U131.5, U132.5, U133.5, U134.5, U135.5, U136.5, U137.5, U138.5, U139.5, U140.5, U141.5, U142.5, U143.5, U144.5, U145.5, U146.5, U147.5, U148.5, U149.5, U150.5, U151.5, U152.5, U153.5, U154.5, U155.5, U156.5, U157.5, U158.5, U159.5, U160.5, U161.5, U162.5, U163.5, U164.5, U165.5, U166.5, U167.5, U168.5, U169.5, U170.5, U171.5, U172.5, U173.5, U174.5, U175.5, U176.5, U177.5, U178.5, U179.5, U180.5, U181.5, U182.5, U183.5, U184.5, U185.5, U186.5, U187.5, U188.5, U189.5, U190.5, U191.5, U192.5, U193.5, U194.5, U195.5, U196.5, U197.5, U198.5, U199.5, U200.5, U201.5, U202.5, U203.5, U204.5, U205.5, U206.5, U207.5, U208.5, U209.5, U210.5, U211.5, U212.5, U213.5, U214.5, U215.5, U216.5, U217.5, U218.5, U219.5, U221.5, U222.5, U223.5, U224.5, U225.5, U226.5

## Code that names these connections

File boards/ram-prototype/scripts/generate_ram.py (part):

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        b.add_wire(pb[0], pb[1], lx, pb[1])
        b.add_label("nA0" if a0_inv else "A0", lx, pb[1])

    # DEC3 output LEDs + local labels for DEC3_0..3 (used) + hier labels for DEC3_4..7 (unused)
    dec3_out_x = snap(dec3_l2_x + 12.70)
    dec3_led_x = snap(dec3_out_x + 2 * GRID)
    dec3_hl_x  = snap(dec3_led_x + 8 * GRID)  # hier labels near LED, not at far-right
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        b.add_wire(pb[0], pb[1], lx_ha, pb[1])
        b.add_label(f"HA{ha_idx}", lx_ha, pb[1])

    # DEC4 output LEDs + local label for DEC4_0 (used) + hier labels for DEC4_1..15 (unused)
    dec4_out_x = snap(dec4_l2_x + 12.70)
    dec4_led_x = snap(dec4_out_x + 2 * GRID)
    dec4_hl_x  = snap(dec4_led_x + 8 * GRID)  # hier labels near LED, not at far-right
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            # Used internally → local label for final cross-product
            label_x = snap(dec4_led_x + GRID)
            b.add_wire(dec4_led_x, out[1], label_x, out[1])
            b.add_label("DEC4_0", label_x, out[1])
        else:
            # Unused → hier label near the LED output
            b.add_wire(dec4_led_x, out[1], dec4_hl_x, out[1])
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
    for sel_idx in range(4):
        pa = final_pins[sel_idx]["1"]   # DEC3_i input
        pb = final_pins[sel_idx]["2"]   # DEC4_0 input
        lx = snap(pa[0] - 4 * GRID)
        b.add_wire(pa[0], pa[1], lx, pa[1])
        b.add_label(f"DEC3_{sel_idx}", lx, pa[1])
        lx = snap(pb[0] - 4 * GRID)
        b.add_wire(pb[0], pb[1], lx, pb[1])
        b.add_label("DEC4_0", lx, pb[1])

    # ================================================================
    # ROW_SEL outputs: final AND output → LED → hier label
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    and3_y = and2_y

    # -- Hier labels for inputs -> wire to inverter inputs --
    b.add_hier_label("nCE", base_x, ce_y, shape="input", justify="right")
    _, ce_inv_pins = b.place_symbol("74LVC1G04", inv_x, ce_y)
    b.connect_power(ce_inv_pins)
    ce_inv_in = ce_inv_pins["2"]
    b.add_wire(base_x, ce_y, ce_inv_in[0], ce_inv_in[1])

    b.add_hier_label("nOE", base_x, oe_y, shape="input", justify="right")
    _, oe_inv_pins = b.place_symbol("74LVC1G04", inv_x, oe_y)
    b.connect_power(oe_inv_pins)
    oe_inv_in = oe_inv_pins["2"]
    b.add_wire(base_x, oe_y, oe_inv_in[0], oe_inv_in[1])

    nwe_jct_x = base_x + 8 * GRID
    b.add_hier_label("nWE", base_x, we_y, shape="input", justify="right")
    _, we_inv_pins = b.place_symbol("74LVC1G04", inv_x, we_y)
    b.connect_power(we_inv_pins)
    we_inv_in = we_inv_pins["2"]
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    b.add_wire(and3_b[0], nwe_route_y, and3_b[0], and3_b[1])
    b.add_junction(nwe_jct_x, we_y)

    # -- AND1 output -> LED T-junction -> hier label WRITE_ACTIVE --
    out_label_x = and3_x + 22 * GRID
    and1_led_x = snap(and1_out[0] + 2 * GRID)
    b.add_wire(and1_out[0], and1_out[1], and1_led_x, and1_out[1])
    b.add_wire(and1_led_x, and1_out[1], out_label_x, and1_out[1])
    b.place_led_below(and1_led_x, and1_out[1])
    b.add_hier_label("WRITE_ACTIVE", out_label_x, and1_out[1], shape="output", justify="left")

    # -- AND3 output -> LED T-junction -> hier label READ_EN --
    and3_led_x = snap(and3_out[0] + 2 * GRID)
    b.add_wire(and3_out[0], and3_out[1], and3_led_x, and3_out[1])
    b.add_wire(and3_led_x, and3_out[1], out_label_x, and3_out[1])
    b.place_led_below(and3_led_x, and3_out[1])
    b.add_hier_label("READ_EN", out_label_x, and3_out[1], shape="output", justify="left")

    return b

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
    b.add_hier_label("ROW_SEL", base_x, row_sel_y,
                     shape="input", justify="right")
    b.add_hier_label("WRITE_ACTIVE", base_x, wa_y,
                     shape="input", justify="right")
    b.add_hier_label("READ_EN", base_x, re_y,
                     shape="input", justify="right")

    # -- AND1: WRITE_EN_ROW = AND(WRITE_ACTIVE, ROW_SEL) --
    and1_y = snap(base_y + 4 * GRID)
    _, and1_pins = b.place_symbol("74LVC1G08", and_x, and1_y)
    b.connect_power(and1_pins)
    and1_a = and1_pins["1"]  # WRITE_ACTIVE
    and1_b = and1_pins["2"]  # ROW_SEL
    and1_out = and1_pins["4"]

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    and2_y = snap(and1_y + SYM_SPACING_Y)
    _, and2_pins = b.place_symbol("74LVC1G08", and_x, and2_y)
    b.connect_power(and2_pins)
    and2_a = and2_pins["1"]  # READ_EN
    and2_b = and2_pins["2"]  # ROW_SEL
    and2_out = and2_pins["4"]

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    b.add_wire(row_trunk_x, and1_b[1], and1_b[0], and1_b[1])
    b.add_wire(row_trunk_x, and2_b[1], and2_b[0], and2_b[1])

    # -- Wire WRITE_ACTIVE to AND1 pin A --
    wa_vert_x = snap(and1_a[0] - GRID)
    b.add_wire(base_x, wa_y, wa_vert_x, wa_y)
    if abs(wa_y - and1_a[1]) > 0.01:
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    else:
        b.add_wire(wa_vert_x, wa_y, and1_a[0], and1_a[1])

    # -- Wire READ_EN to AND2 pin A --
    re_vert_x = snap(and2_a[0] - GRID)
    b.add_wire(base_x, re_y, re_vert_x, re_y)
    if abs(re_y - and2_a[1]) > 0.01:
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    """
    Root sheet: 24-pin connector, bus indicator LEDs, pin headers, hierarchy refs.

    Connector pin order: GND, A0-A6, nCE/nWE/nOE, D0-D7, A7-A10, VCC

    Layout:
      - Col1: Address Decoder, Column Select (stacked)
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
    # ================================================================
    # Connector pin mapping (24-pin)
    # Pin 1=GND, 2-5=A7-A10, 6-8=nWE/nOE/nCE, 9-16=D0-D7, 17-23=A0-A6, 24=VCC
    # At 180° orientation: pin 24 (VCC) at top, pin 1 (GND) at bottom
    # Visual top-to-bottom: VCC, A0-A6, D0-D7, nCE/nOE/nWE, A7-A10, GND
    # ================================================================
    signal_names = [
        "A7", "A8", "A9", "A10",                           # pins 2-5
        "nWE", "nOE", "nCE",                               # pins 6-8
        "D0", "D1", "D2", "D3", "D4", "D5", "D6", "D7",  # pins 9-16
        "A0", "A1", "A2", "A3", "A4", "A5", "A6",         # pins 17-23
    ]
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
    # Direct wire destinations:
    # A0-A6 → Address Decoder, A7-A10 → Column Select
    # nCE/nOE/nWE use labels (Control Logic is below row control, too far for direct wires)
    direct_wire_dest = {}
    for i in range(7):
        direct_wire_dest[f"A{i}"] = addr_pp[f"A{i}"]
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            b.add_wire(dtx, ty, dtx, dest_py)
            b.add_wire(dtx, dest_py, dest_px, dest_py)
        else:
            # D0-D7 and nCE/nOE/nWE use labels
            b.add_wire(led_jct_x, ty, label_x, ty)
            b.add_label(sig, label_x, ty)

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        b.add_wire(tx, dst_y, dst_x, dst_y)

    # ================================================================
    # Route: Connector → Control Logic (nCE/nOE/nWE via labels)
    # ================================================================
    for sig in ["nCE", "nOE", "nWE"]:
        px, py = ctrl_pp[sig]
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        b.add_label(sig, px - wire_stub, py, justify="right")

    # ================================================================
    # Route: Control Logic RIGHT → Row Control LEFT (WRITE_ACTIVE, READ_EN via labels)
    #
    # KiCad 10 ERC flags a label as dangling unless its net contains a
    # symbol pin in the **same** sheet (sub-sheet pins inside hierarchy
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    # ================================================================
    wa_src = ctrl_pp["WRITE_ACTIVE"]
    b.add_wire(wa_src[0], wa_src[1], wa_src[0] + wire_stub, wa_src[1])
    b.add_label("WRITE_ACTIVE", wa_src[0] + wire_stub, wa_src[1])
    b.place_pin_anchor(wa_src[0] + wire_stub, wa_src[1])
    for i in range(4):
        d = rc_pp[i]["WRITE_ACTIVE"]
        b.add_wire(d[0], d[1], d[0] - wire_stub, d[1])
        b.add_label("WRITE_ACTIVE", d[0] - wire_stub, d[1], justify="right")

    re_src = ctrl_pp["READ_EN"]
    b.add_wire(re_src[0], re_src[1], re_src[0] + wire_stub, re_src[1])
    b.add_label("READ_EN", re_src[0] + wire_stub, re_src[1])
    b.place_pin_anchor(re_src[0] + wire_stub, re_src[1])
    for i in range(4):
        d = rc_pp[i]["READ_EN"]
        b.add_wire(d[0], d[1], d[0] - wire_stub, d[1])
        b.add_label("READ_EN", d[0] - wire_stub, d[1], justify="right")

    # ================================================================
    # Route: Col2 RIGHT → Bytes (WRITE_EN_ROW_i, READ_EN_ROW_i)
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            b.add_label(ren_sig, dst_x - wire_stub, dst_y, justify="right")

    # ================================================================
    # Route: COL_SEL_0 → bytes 0-3, COL_SEL_1 → bytes 4-7 via labels
    # ================================================================
    for col_j in range(2):
        col_sig = f"COL_SEL_{col_j}"
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                                        in_bom=False)

    for pin_idx in range(14):
        col_idx = pin_idx + 2  # COL_SEL_2 through COL_SEL_15
        sig = f"COL_SEL_{col_idx}"
        pin_num = str(pin_idx + 1)
        px, py = colsel_hdr_pins[pin_num]
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
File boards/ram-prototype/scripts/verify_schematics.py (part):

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        if not on_same_net(rc, by1):
            issues.append(f"  {rc} not connected to {by1}")

    # 6. COL_SEL_0 -> bytes 0-3, COL_SEL_1 -> bytes 4-7 (via labels)
    for col_j in range(2):
        lbl = f"label:COL_SEL_{col_j}"
        for row_i in range(4):
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        if not id_exists(cl):
            issues.append(f"  {cl} not found in any net")

    # 11. DEC3_4-7: addr decoder -> unused 3-to-8 header (via labels)
    for i in range(4, 8):
        sig = f"DEC3_{i}"
        ad = f"Address Decoder:{sig}"
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        if not on_same_net(ad, lbl):
            issues.append(f"  {ad} not connected to label:{sig}")

    # 12. DEC4_1-15: addr decoder -> unused 4-to-16 header (via labels)
    for i in range(1, 16):
        sig = f"DEC4_{i}"
        ad = f"Address Decoder:{sig}"
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        if not on_same_net(ad, lbl):
            issues.append(f"  {ad} not connected to label:{sig}")

    # 13. COL_SEL_2-15: col select -> unused column header (via labels)
    for col_idx in range(2, 16):
        sig = f"COL_SEL_{col_idx}"
        cs = f"Column Select:{sig}"
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        ("Row Control 0:WRITE_EN_ROW", "Row Control 1:WRITE_EN_ROW"),
        ("Row Control 0:READ_EN_ROW", "Row Control 1:READ_EN_ROW"),
        # COL_SEL lines isolated
        ("label:COL_SEL_0", "label:COL_SEL_1"),
        ("label:COL_SEL_0", "label:COL_SEL_15"),
        # Cross-domain isolation
        ("label:D0", "Address Decoder:A0"),
        ("label:D0", "Control Logic:nCE"),
        ("Control Logic:WRITE_ACTIVE", "Control Logic:READ_EN"),
        # DEC3/DEC4 unused outputs isolated from each other
        ("label:DEC3_4", "label:DEC3_5"),
        ("label:DEC4_1", "label:DEC4_2"),
    ]
    for id_a, id_b in isolation_pairs:
        if on_same_net(id_a, id_b):
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
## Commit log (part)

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2026-02-22 Initial Claude setup
2026-02-22 Switch to little logic chips
2026-02-22 Initial implementation of RAM prototype
2026-02-23 Partway through erc debugging
2026-02-23 Fix all ERC checks
2026-02-23 fix duplicate id issues
2026-02-23 Start cleaning up the schematic
2026-02-23 Schematic is starting to look good
2026-02-23 Fix ERC issues
2026-02-23 Create verification script
2026-02-24 Reformat with kicad
2026-02-24 Fix a bunch of issues
2026-02-24 Clean up root
2026-02-24 Continue with updates
2026-02-25 More reasonable top level designrout
2026-02-25 Clean up root more and add more data
2026-02-25 fixup root page
2026-02-25 Update claude.md with lessons and instructions to keep it up to date
2026-02-27 add and fix some checks
2026-02-27 Fix labelling
2026-02-27 add additional bounding box verification
2026-02-27 fix remaining warnings
2026-02-27 fix fanout
2026-02-27 move common functions to a shared library
2026-02-27 Initial pcb generation implementation
2026-02-27 fix a lot of issues
2026-02-28 fix location of pcb
2026-02-28 Additinitial implementation of routing
2026-03-01 pre-route part of the wires to speed up auto routing
2026-03-01 Fix errors from autorouting
2026-03-01 Fix some pcb drc warnings
2026-03-01 Fix more drc errors
2026-03-01 fix some of the routing
2026-03-01 rearange some components
2026-03-02 Clean up silkscreen
2026-03-02 update design rules and make verification script stricter
2026-03-03 fix many issues
2026-03-04 improve routing
2026-03-04 Compact the ram and make it look good
2026-03-08 Add pcb test section
2026-03-08 fix issues
2026-03-08 flip resistor to the back
2026-03-08 fix minor issue
2026-03-09 Fix some layer issues
2026-03-09 Update schematic with new row/col architecture
2026-03-09 layout 8 pin byte control
2026-03-10 route column selects
2026-03-10 clean up routing
2026-03-10 more cleanup
2026-03-10 rotate buffer and flip flop for better routing
2026-03-10 Change layout
2026-03-10 refactor read and write schematics into row control sheets
2026-03-11 Add initial changes to make logic close to final
2026-03-11 clean up
2026-03-11 Update row select to have the full complexity to test latency
2026-03-11 Fix more issues
2026-03-11 better column select led layout
2026-03-11 update row select spacing
2026-03-11 update todos
2026-03-11 reduce footprint sizes
2026-03-11 Fix rotation confusion
2026-03-11 Fix weird angles
2026-03-11 compress vertically
2026-03-12 fix pin numbering
2026-03-12 Add visual inspection tooling
2026-03-12 Make scripts work with each other more
2026-03-12 Fixup claude.md
2026-03-12 bring resistor to front
2026-03-12 Clean up warning skip list
2026-03-12 route leds
2026-03-14 Compress ram cells
2026-03-14 route between flipflop and buffer
2026-03-15 Add png paths to output
2026-03-15 Add JLCPCB to verify
2026-03-16 fix warnings
2026-03-16 minor cleanup
2026-03-16 route gnd traces
2026-03-16 put vias in the correct spot
2026-03-16 fix some routing issues
2026-03-16 Fix most issues
2026-03-16 route vcc
2026-03-17 finish routing front of the ram cells
2026-03-17 move dsbga8
2026-03-17 fix leds and compress bytes
2026-03-17 add horizontal traces
2026-03-29 add a way to make buses
2026-03-29 fix settings files
2026-03-29 add todos
2026-03-31 fix layout
2026-04-01 remove accidentally committed temp file
